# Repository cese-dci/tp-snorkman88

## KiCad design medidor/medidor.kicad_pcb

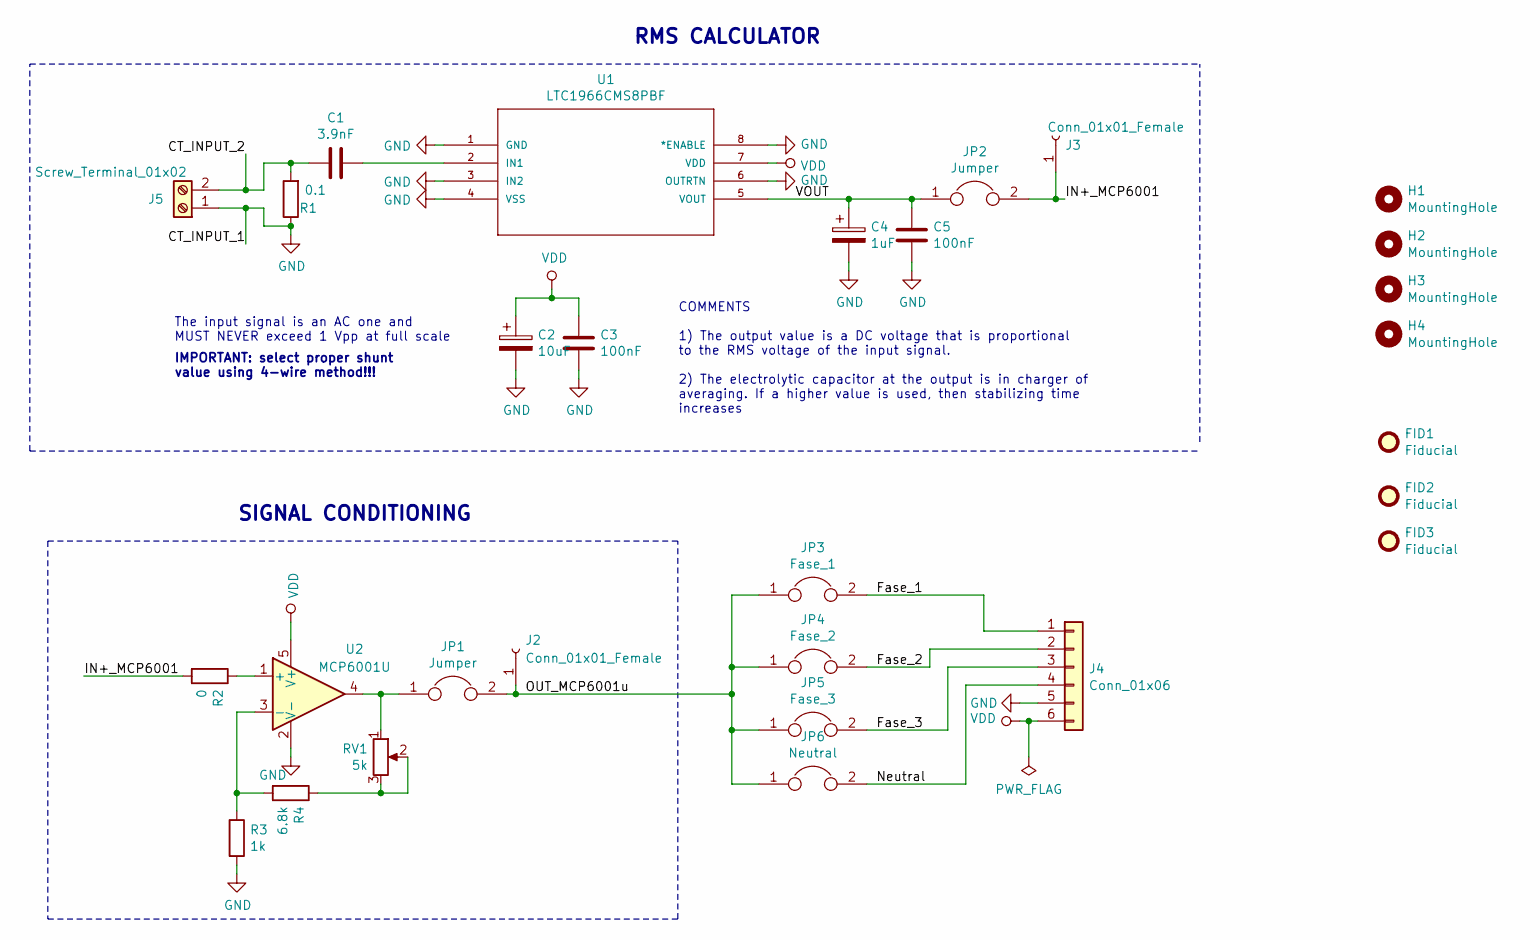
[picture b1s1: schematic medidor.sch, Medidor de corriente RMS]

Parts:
C1: 3.9nF; C_1206_3216Metric_Pad1.42x1.75mm_HandSolder
C2: 10uF; CP_Elec_6.3x4.9
C3, C5: 100nF; C_0805_2012Metric_Pad1.15x1.40mm_HandSolder
C4: 1uF; CP_Elec_6.3x4.9
FID1, FID2, FID3: Fiducial; Fiducial_1.5mm_Mask4.5mm
H1, H2, H3, H4: MountingHole; MountingHole_4.3mm_M4
J2, J3: Conn_01x01_Female; PinHeader_1x01_P2.54mm_Vertical
J4: Conn_01x06; PinHeader_1x06_P2.54mm_Vertical
J5: Screw_Terminal_01x02; TerminalBlock_MetzConnect_Type703_RT10N02HGLU_1x02_P9.52mm_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
JP1, JP2: Jumper; SolderJumper-2_P1.3mm_Open_RoundedPad1.0x1.5mm
JP3: Fase_1; SolderJumper-2_P1.3mm_Open_RoundedPad1.0x1.5mm
JP4: Fase_2; SolderJumper-2_P1.3mm_Open_RoundedPad1.0x1.5mm
JP5: Fase_3; SolderJumper-2_P1.3mm_Open_RoundedPad1.0x1.5mm
JP6: Neutral; SolderJumper-2_P1.3mm_Open_RoundedPad1.0x1.5mm
R1: 0.1; TO-220-2_Vertical; Digikey_Code PWR221T-30-R100F-ND
R2: 0; R_0805_2012Metric_Pad1.15x1.40mm_HandSolder
R3: 1k; R_0805_2012Metric_Pad1.15x1.40mm_HandSolder
R4: 6.8k; R_0805_2012Metric_Pad1.15x1.40mm_HandSolder
RV1: 5k; Potentiometer_Bourns_TC33X_Vertical; Digikey_Code P3V502CT-ND
U1: LTC1966CMS8PBF; MSOP-8_MS; MANUFACTURER_PART_NUMBER ltc1966cms8#pbf; Digikey_Code LTC1966CMS8#PBF-ND
U2: MCP6001U; SOT-353_SC-70-5_Handsoldering; Digikey_Code MCP6001UT-I/OTCT-ND

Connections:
/CT_INPUT_2: C1.2, J5.2, R1.2
/Fase_1: J4.1, JP3.2
/Fase_2: J4.2, JP4.2
/Fase_3: J4.3, JP5.2
/IN+_MCP6001: J3.1, JP2.2, R2.2
/Neutral: J4.4, JP6.2
/OUT_MCP6001u: J2.1, JP1.2, JP3.1, JP4.1, JP5.1, JP6.1
/VOUT: C4.1, C5.1, JP2.1, U1.5 (VOUT)
GND: C2.2, C3.2, C4.2, C5.2, J4.5, J5.1, R1.1, R3.2, U1.1 (GND), U1.3 (IN2), U1.4 (VSS), U1.6 (OUTRTN), U1.8 (*ENABLE), U2.2 (V-)
unnamed: C1.1, U1.2 (IN1)
unnamed: JP1.1, RV1.1, U2.4
unnamed: R2.1, U2.1 (+)
unnamed: R3.1, R4.2, U2.3 (-)
unnamed: R4.1, RV1.2, RV1.3
VDD: C2.1, C3.1, J4.6, U1.7 (VDD), U2.5 (V+)

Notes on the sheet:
RMS CALCULATOR
SIGNAL CONDITIONING
The input signal is an AC one and MUST NEVER exceed 1 Vpp at full scale
COMMENTS 1) The output value is a DC voltage that is proportional to the RMS voltage of the input signal. 2) The electrolytic capacitor at the output is in charger of averaging. If a higher value is used, then stabilizing time increases
IMPORTANT: select proper shunt value using 4-wire method!!!

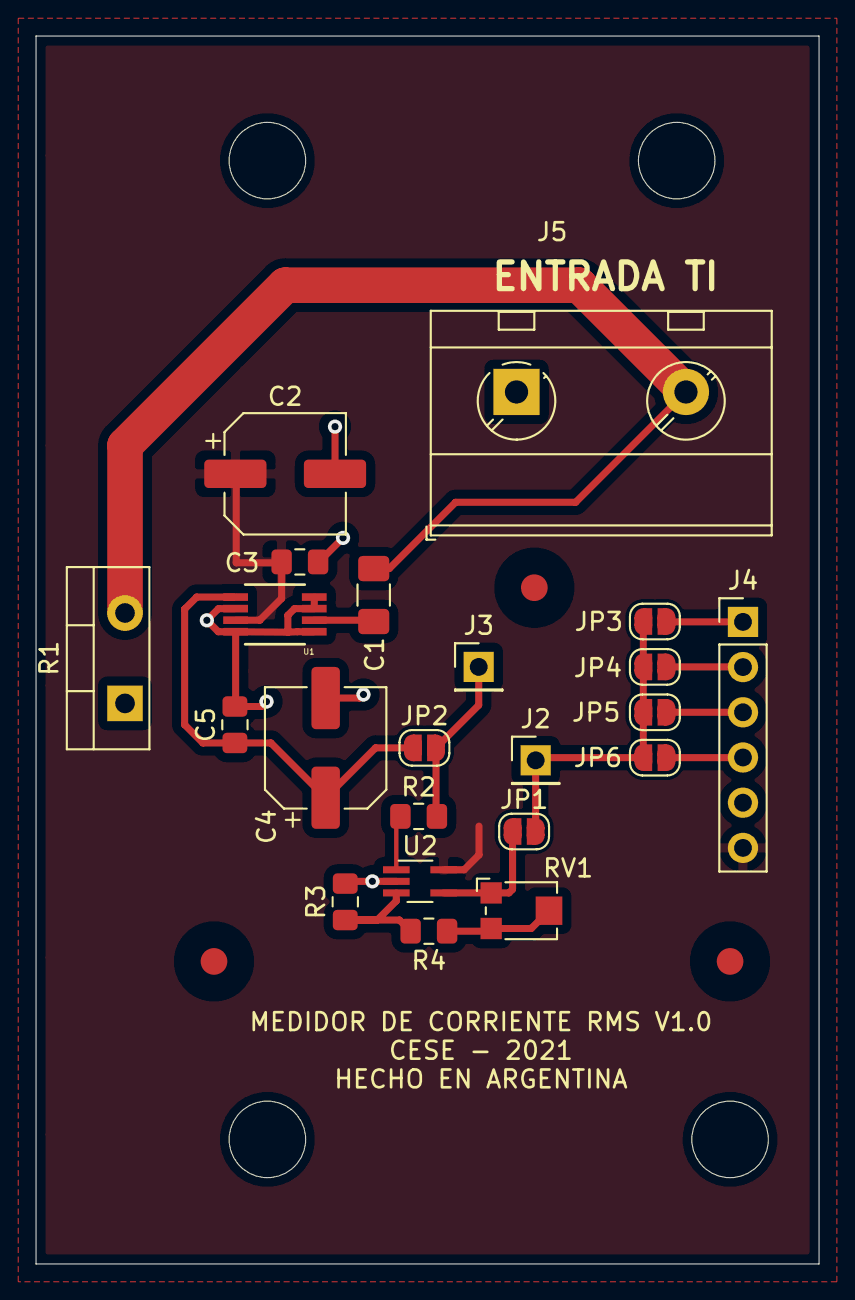
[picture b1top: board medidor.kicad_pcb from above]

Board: 2 copper layers, 44.0 x 69.0 mm, 29 parts (0 on the bottom side), 15 nets.

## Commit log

2021-04-02 Se agrega readme
2021-04-02 primer commit
    se presenta el primer esquematico
2021-04-02 Se asocian los footprints
2021-04-12 Se agrega ruteo pcb y recuadros para cada parte dell esquematico
2021-04-13 Se agrega PWR_FLAG para solucionar error de ERC
2021-04-13 Se agregan cotas al PCB
2021-04-13 Se agregan fiduciarios
2021-04-13 Se agrega leyenda en serigrafia
2021-04-13 Se agregan datos en rotulo
2021-04-13 Se agrega revisor en rotulo
2021-04-21 Se agrega carpeta con info adicional del proyecto.
2021-04-21 Se agregan correcciones sugeridas por el docente y se define la version con shunt TO-220-2

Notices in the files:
medidor/medidor.kicad_pcb:
Released under the Creative Commons Attribution Share-Alike 4.0 Licence
medidor/medidor.sch:
https://creativecommons.org/license/by-sa/4.0
parts and their libraries:
Copyright C 2016 Accelerated Designs. All rights reserved
